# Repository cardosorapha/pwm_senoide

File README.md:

# Gerador Senoidal PWM

Esta é uma placa contendo o circuito de uma ponte H transistorizada com base no MOSFET IRF540N. No [esquemático](./pwm_seno.pdf), as conexões estão descritas e separadas em blocos, que fizeram parte do projeto da PCB. Para montar o projeto, uma lista de materiais interativa está disponível [aqui](https://cardosorapha.github.io/pwm_senoide/).

## Uso

* O projeto para STM32 que gera sinais interpretados por essa placa pode ser encontrado [aqui](https://github.com/cardosorapha/sin_stm). 
* Você pode utilizar qualquer outra forma de geração de PWM para utilizar esta placa.
* Atenção à potência máxima na saída, calculada como VDC^2/2RL.

### Alimentação

* +12V indicado por +VDC
* GND

### Entradas

* Dois sinais de controle PWM 1 e 2
* GND

### Saídas

* Speaker

### Fabricação

Os arquivos gerber estão disponíveis na pasta [gerbers](./gerbers) para fabricação. 

## Customização

Pré-requisitos:
* [KiCAD](https://kicad-pcb.org/)

O projeto pode ser facilmente clonado com:
```
git clone https://github.com/cardosorapha/pwm_senoide.git
```

## Contato

Raphael Cardoso - cardosodeoliveir@gmail.com

Link do Projeto: [https://github.com/cardosorapha/pwm_senoide](https://github.com/cardosorapha/pwm_senoide)

# Desenvolvido na

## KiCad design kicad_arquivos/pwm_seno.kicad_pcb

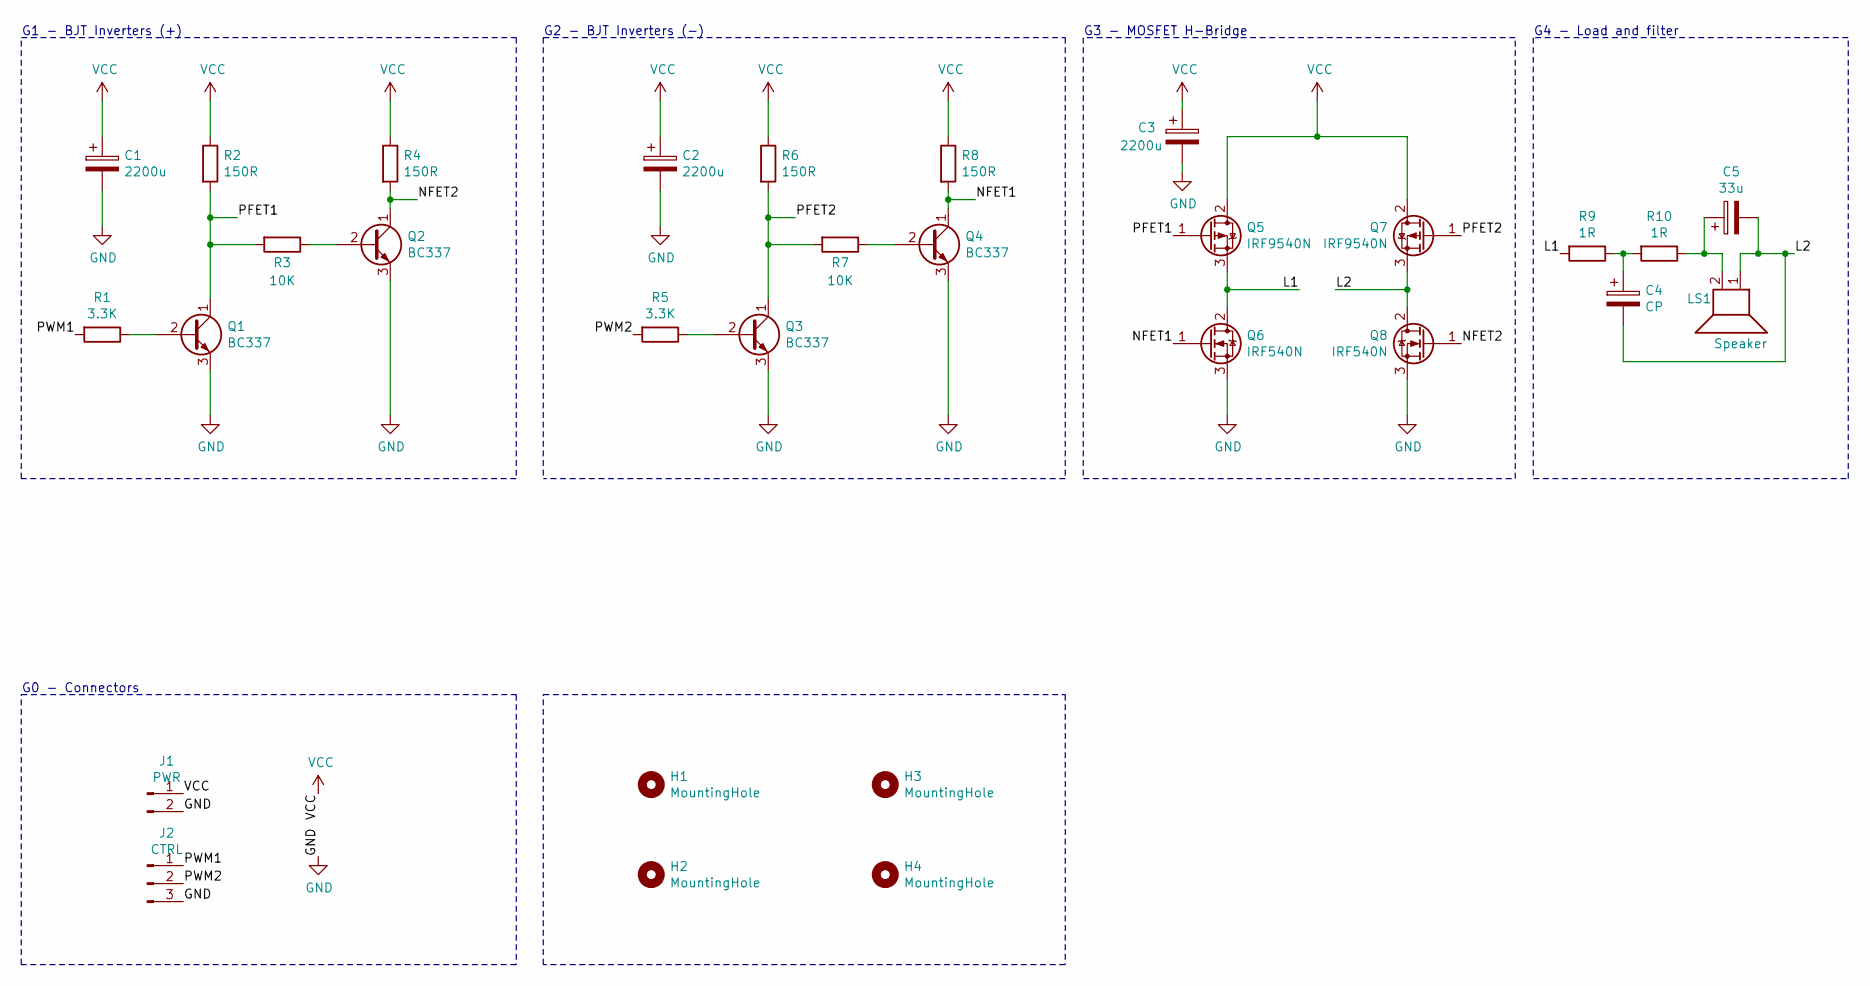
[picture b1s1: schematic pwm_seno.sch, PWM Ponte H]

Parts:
C1, C2, C3: 2200u; CP_Radial_D24.0mm_P10.00mm_SnapIn
C4: CP; CP_Radial_D8.0mm_P3.80mm
C5: 33u; CP_Radial_D8.0mm_P3.80mm
H1, H2, H3, H4: MountingHole; MountingHole_3.2mm_M3
J1: PWR; TerminalBlock_bornier-2_P5.08mm
J2: CTRL; TerminalBlock_bornier-3_P5.08mm
LS1: Speaker; TerminalBlock_bornier-2_P5.08mm
Q1, Q2, Q3, Q4: BC337; TO-92_Inline_Wide
Q5, Q7: IRF9540N; TO-220-3_Vertical
Q6, Q8: IRF540N; TO-220-3_Vertical
R1, R5: 3.3K; R_Axial_DIN0207_L6.3mm_D2.5mm_P10.16mm_Horizontal
R2, R4, R6, R8: 150R; R_Axial_DIN0414_L11.9mm_D4.5mm_P20.32mm_Horizontal
R3, R7: 10K; R_Axial_DIN0207_L6.3mm_D2.5mm_P10.16mm_Horizontal
R9, R10: 1R; R_Axial_DIN0922_L20.0mm_D9.0mm_P30.48mm_Horizontal

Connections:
/L1: Q5.3 (S), Q6.2 (D), R9.2
/L2: C4.2, C5.2, LS1.1, Q7.3 (S), Q8.2 (D)
/NFET1: Q4.1 (C), Q6.1 (G), R8.2
/NFET2: Q2.1 (C), Q8.1 (G), R4.2
/PFET1: Q1.1 (C), Q5.1 (G), R2.2, R3.2
/PFET2: Q3.1 (C), Q7.1 (G), R6.2, R7.2
/PWM1: J2.1, R1.2
/PWM2: J2.2, R5.2
GND: C1.2, C2.2, C3.2, J1.2, J2.3, Q1.3 (E), Q2.3 (E), Q3.3 (E), Q4.3 (E), Q6.3 (S), Q8.3 (S)
unnamed: C4.1, R9.1, R10.2
unnamed: C5.1, LS1.2, R10.1
unnamed: Q1.2 (B), R1.1
unnamed: Q2.2 (B), R3.1
unnamed: Q3.2 (B), R5.1
unnamed: Q4.2 (B), R7.1
VCC: C1.1, C2.1, C3.1, J1.1, Q5.2 (D), Q7.2 (D), R2.1, R4.1, R6.1, R8.1

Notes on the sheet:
G0 - Connectors
G1 - BJT Inverters (+)
G2 - BJT Inverters (-)
G3 - MOSFET H-Bridge
G4 - Load and filter

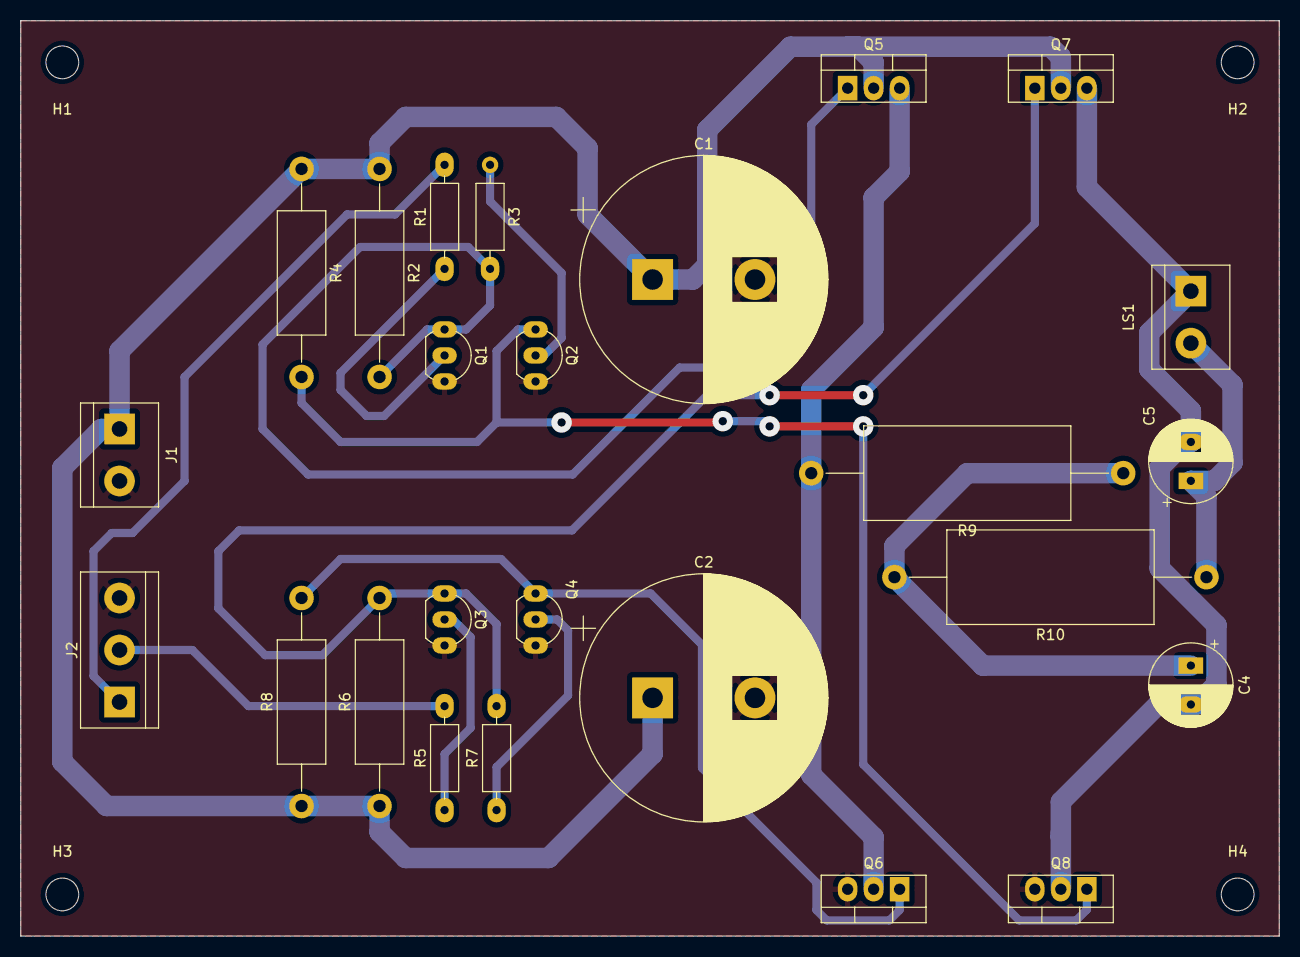
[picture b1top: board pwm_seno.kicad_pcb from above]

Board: 2 copper layers, 122.9 x 89.4 mm, 29 parts (0 on the bottom side), 16 nets.

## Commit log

2020-07-22 Criado esquemático
2020-07-22 Modificado nome da pasta, footprints adicionadas e netlist gerada.
2020-07-22 Adicionados mounting holes e criado arquivo vazio de PCB
2020-07-22 Finalizado roteamento, gerados gerbers e BOM, adicionado esquematico PDF
2020-07-22 Adição de imagens
2020-07-22 Criação de html de montagem
2020-07-22 Atualização do readme
2020-07-22 Adicionado segundo filtro
2020-08-03 Adicionada segunda ordem ao filtro
2020-08-03 Atualizado PDF de esquematico
2020-08-03 Adicionadas imagens de ensaios
2020-08-03 Adicionadas imagens ao readme
